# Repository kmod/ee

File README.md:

ee
==

A catchall repo for my more EE-related projects

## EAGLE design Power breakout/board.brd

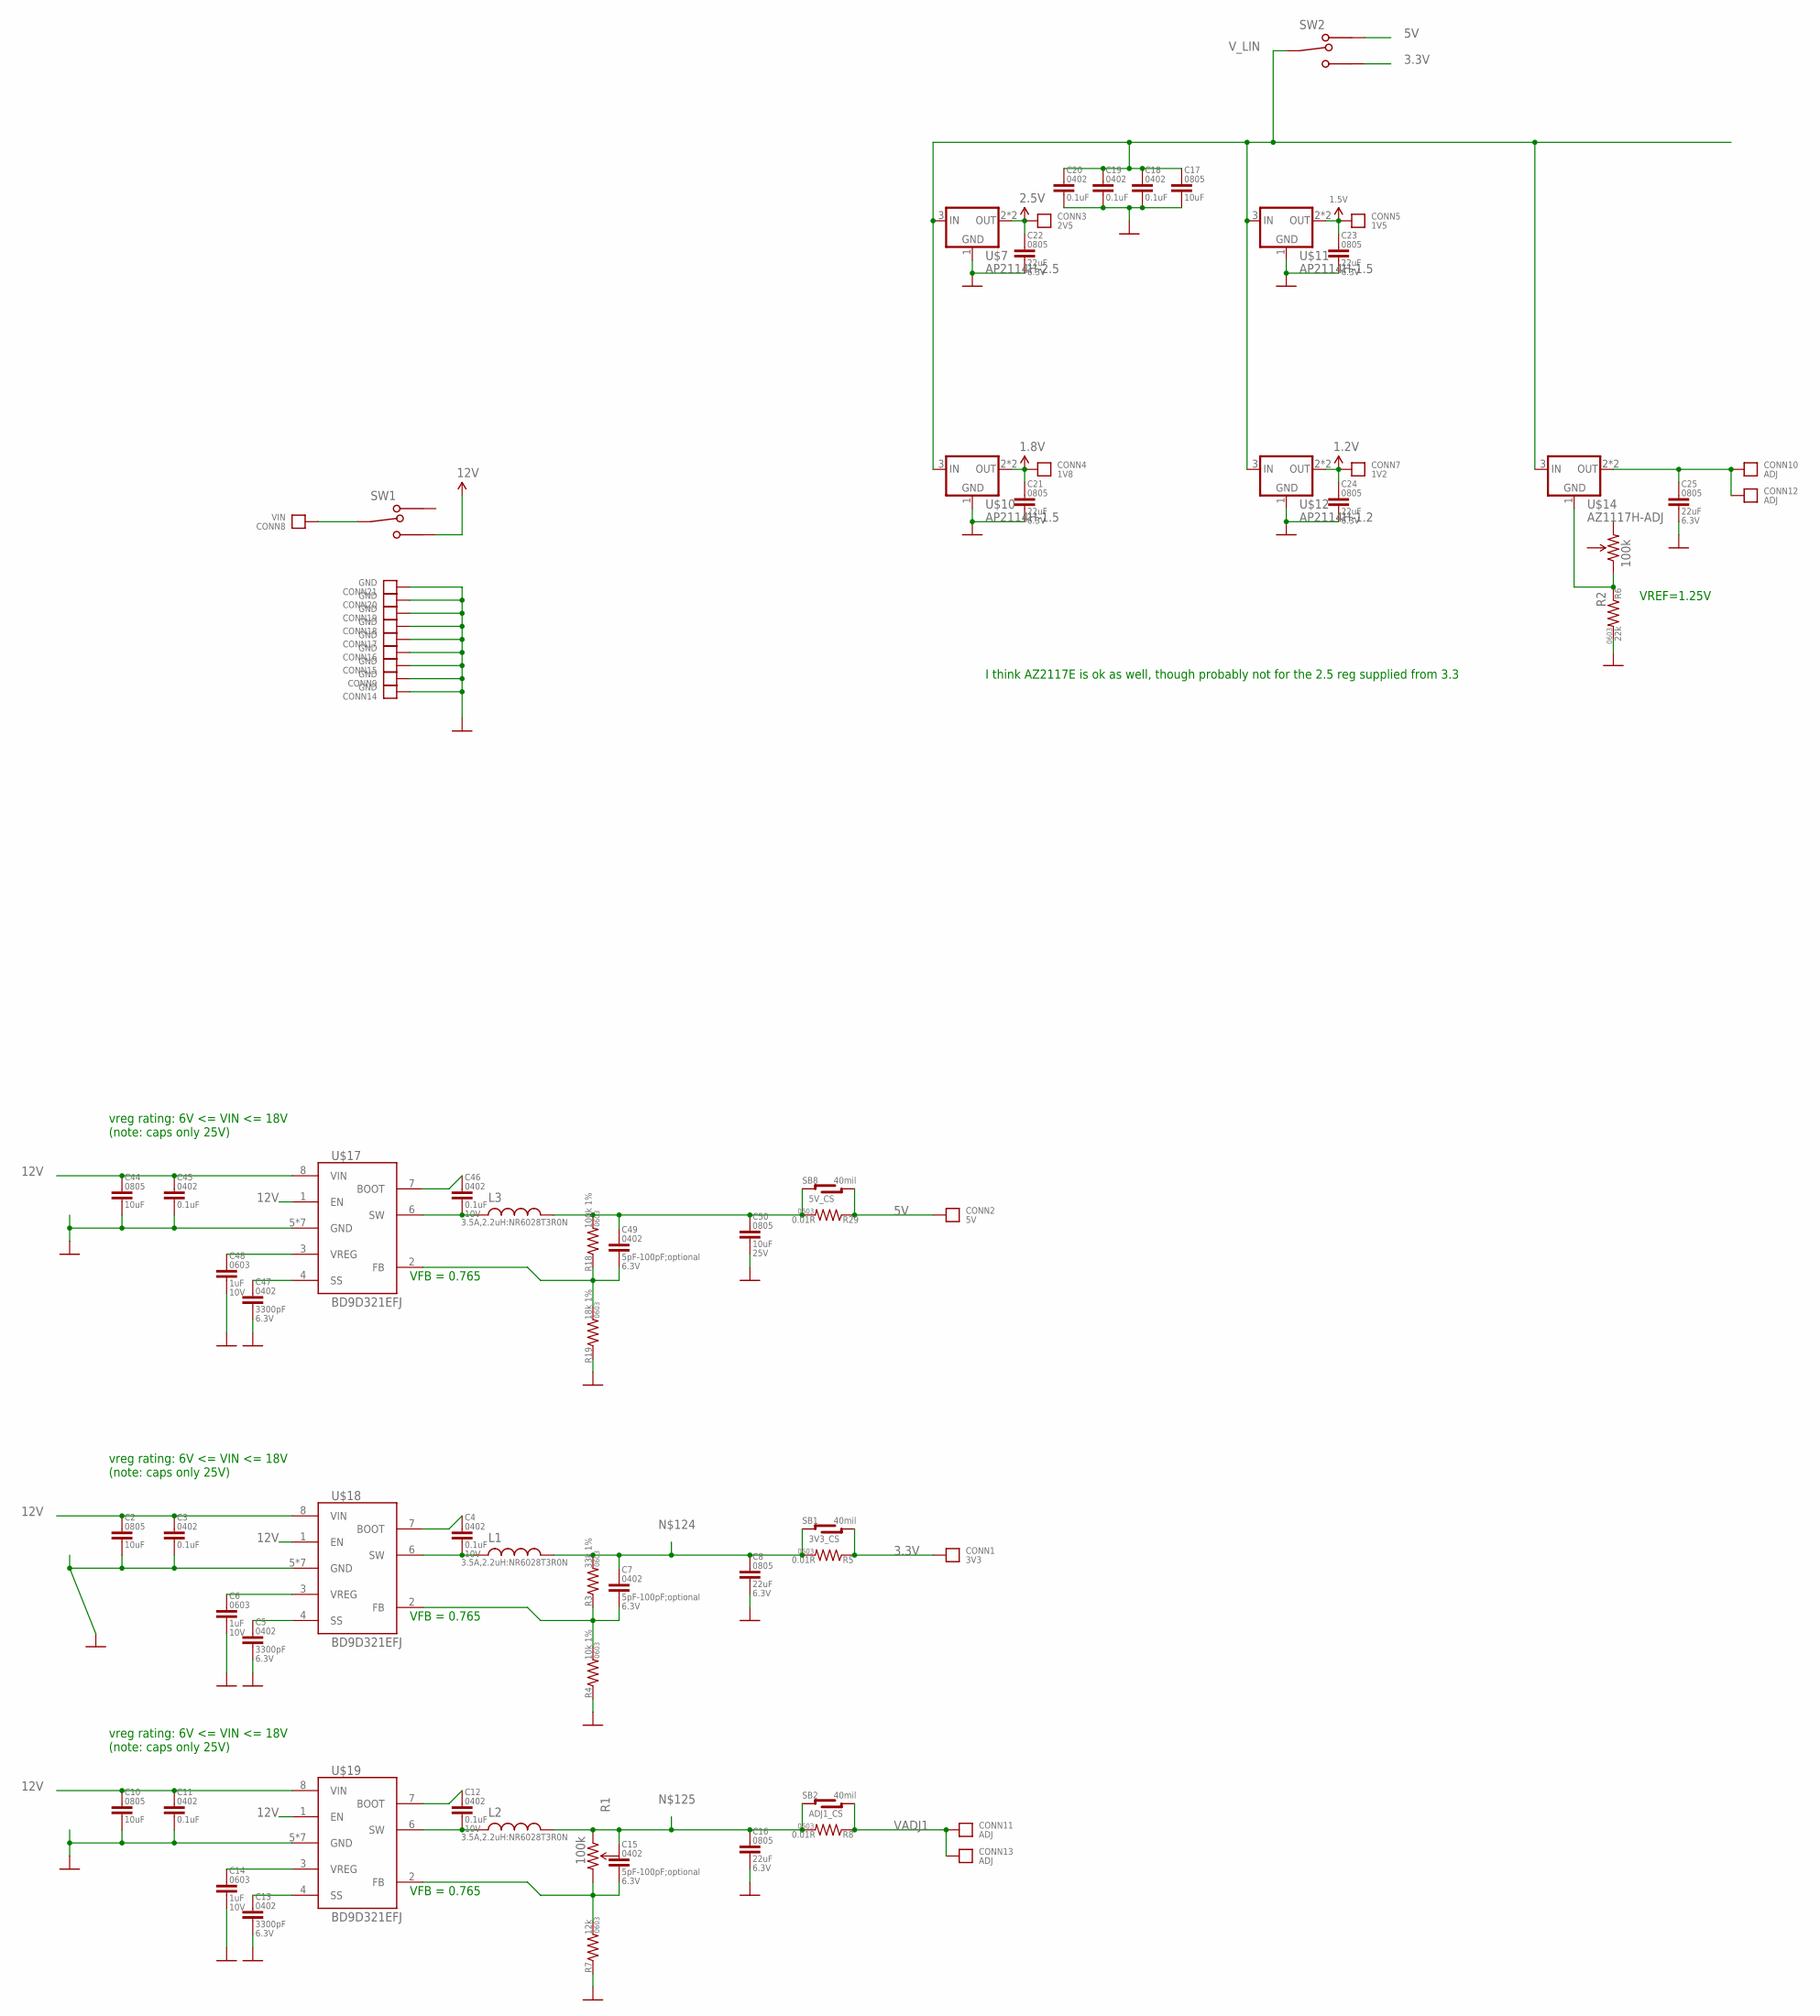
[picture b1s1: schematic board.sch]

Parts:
C2, C10, C17, C44, C50: 10uF; 0805-CAP; VOLTAGE 25V
C3, C11, C18, C19, C20, C45: 0.1uF; 0402-CAP; VOLTAGE 25V
C4, C12, C46: 0.1uF; 0402-CAP; VOLTAGE 10V
C5, C13, C47: 3300pF; 0402-CAP
C6, C14, C48: 1uF; 0603-CAP; VOLTAGE 10V
C7, C15, C49: 5pF-100pF;optional; 0402-CAP
C8, C16, C21, C22, C23, C24, C25: 22uF; 0805-CAP
CONN1: 3V3; HOLE_22AWG
CONN2: 5V; HOLE_22AWG
CONN3: 2V5; HOLE_22AWG
CONN4: 1V8; HOLE_22AWG
CONN5: 1V5; HOLE_22AWG
CONN7: 1V2; HOLE_22AWG
CONN8: VIN; HOLE_22AWG
CONN9, CONN14, CONN15, CONN16, CONN17, CONN18, CONN19, CONN20, CONN21: GND; HOLE_22AWG
CONN10, CONN11: ADJ; HOLE_22AWG
CONN12, CONN13: ADJ; HOLE_28AWG
L1, L2, L3: 3.5A,2.2uH:NR6028T3R0N; NR60XX
R1, R2: 100k; TRIM_POT_PTH
R3: 33k 1%; 0603-RES
R4: 10k 1%; 0603-RES
R5, R8, R29: 0.01R; 0603-RES
R6: 22k; 0603-RES
R7: 12k; 0603-RES
R18: 100k 1%; 0603-RES
R19: 18k 1%; 0603-RES
SB1: 3V3_CS; SOLDER-BRIDGE-OPEN-LARGE
SB2: ADJ1_CS; SOLDER-BRIDGE-OPEN-LARGE
SB8: 5V_CS; SOLDER-BRIDGE-OPEN-LARGE
SW1, SW2: SWITCH_SPDT; SWITCH_SLIDE_SPDT
U$7: AP2114H-2.5; SOT223
U$10, U$11: AP2114H-1.5; SOT223
U$12: AP2114H-1.2; SOT223
U$14: AZ1117H-ADJ; SOT223
U$17, U$18, U$19: BD9D321EFJ; HTSOP8

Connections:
1.2V: C24.1, CONN7.P, U$12.2 (OUT), U$12.4 (OUT)
1.5V: C23.1, CONN5.P, U$11.2 (OUT), U$11.4 (OUT)
1.8V: C21.1, CONN4.P, U$10.2 (OUT), U$10.4 (OUT)
2.5V: C22.1, CONN3.P, U$7.2 (OUT), U$7.4 (OUT)
3.3V: CONN1.P, R5.1, SB1.R1, SB1.R2, SW2.P2
3.3V_FB: C49.2, R18.1, R19.2, U$17.2 (FB)
3.3V_FB1: C7.2, R3.1, R4.2, U$18.2 (FB)
3.3V_FB2: C15.2, R1.3 (CW), R7.2, U$19.2 (FB)
5V: CONN2.P, R29.1, SB8.R1, SB8.R2, SW2.P1
12V: C2.1, C3.1, C10.1, C11.1, C44.1, C45.1, SW1.P2, U$17.1 (EN), U$17.8 (VIN), U$18.1 (EN), U$18.8 (VIN), U$19.1 (EN), U$19.8 (VIN)
GND: C2.2, C3.2, C5.2, C6.2, C8.2, C10.2, C11.2, C13.2, C14.2, C16.2, C17.2, C18.2, C19.2, C20.2, C21.2, C22.2, C23.2, C24.2, C25.2, C44.2, C45.2, C47.2, C48.2, C50.2, CONN9.P, CONN14.P, CONN15.P, CONN16.P, CONN17.P, CONN18.P, CONN19.P, CONN20.P, CONN21.P, R4.1, R6.2, R7.1, R19.1, U$7.1 (GND), U$10.1 (GND), U$11.1 (GND), U$12.1 (GND), U$17.5 (GND), U$17.P$1 (GND), U$17.P$2 (GND), U$17.P$3 (GND), U$17.P$4 (GND), U$17.P$5 (GND), U$17.PAD (GND), U$18.5 (GND), U$18.P$1 (GND), U$18.P$2 (GND), U$18.P$3 (GND), U$18.P$4 (GND), U$18.P$5 (GND), U$18.PAD (GND), U$19.5 (GND), U$19.P$1 (GND), U$19.P$2 (GND), U$19.P$3 (GND), U$19.P$4 (GND), U$19.P$5 (GND), U$19.PAD (GND)
unnamed: C25.1, CONN10.P, CONN12.P, U$14.2 (OUT), U$14.4 (OUT)
unnamed: C4.1, U$18.7 (BOOT)
unnamed: C4.2, L1.P$1 (1), U$18.6 (SW)
unnamed: C6.1, U$18.3 (VREG)
unnamed: C5.1, U$18.4 (SS)
unnamed: C12.1, U$19.7 (BOOT)
unnamed: C12.2, L2.P$1 (1), U$19.6 (SW)
unnamed: C14.1, U$19.3 (VREG)
unnamed: C13.1, U$19.4 (SS)
unnamed: R2.1 (CCW), R6.1, U$14.1 (GND)
unnamed: C46.2, L3.P$1 (1), U$17.6 (SW)
unnamed: C46.1, U$17.7 (BOOT)
unnamed: C48.1, U$17.3 (VREG)
unnamed: C47.1, U$17.4 (SS)
unnamed: C49.1, C50.1, L3.P$2 (2), R18.2, R29.2, SB8.L1, SB8.L2
unnamed: C7.1, C8.1, L1.P$2 (2), R3.2, R5.2, SB1.L1, SB1.L2
unnamed: C15.1, C16.1, L2.P$2 (2), R1.1 (CCW), R8.2, SB2.L1, SB2.L2
VADJ1: CONN11.P, CONN13.P, R8.1, SB2.R1, SB2.R2
VIN_UNSW: CONN8.P, SW1.C
V_LIN: C17.1, C18.1, C19.1, C20.1, SW2.C, U$7.3 (IN), U$10.3 (IN), U$11.3 (IN), U$12.3 (IN), U$14.3 (IN)

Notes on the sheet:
VFB = 0.765
vreg rating: 6V <= VIN <= 18V (note: caps only 25V)
VREF=1.25V
I think AZ2117E is ok as well, though probably not for the 2.5 reg supplied from 3.3

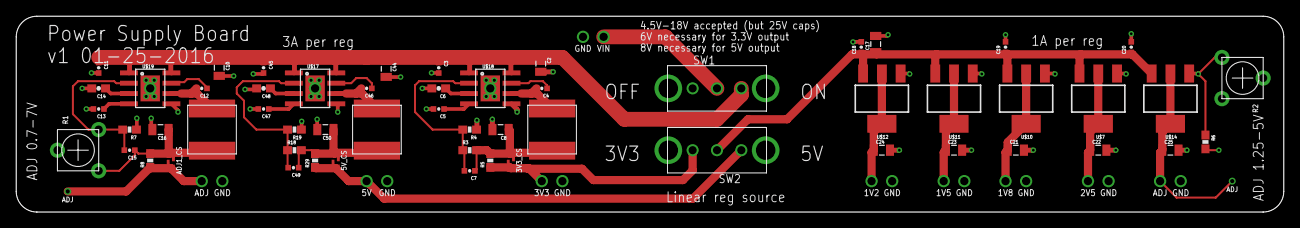
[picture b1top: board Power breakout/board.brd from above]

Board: 2 copper layers, 156.2 x 24.1 mm, 77 parts (0 on the bottom side), 31 nets.

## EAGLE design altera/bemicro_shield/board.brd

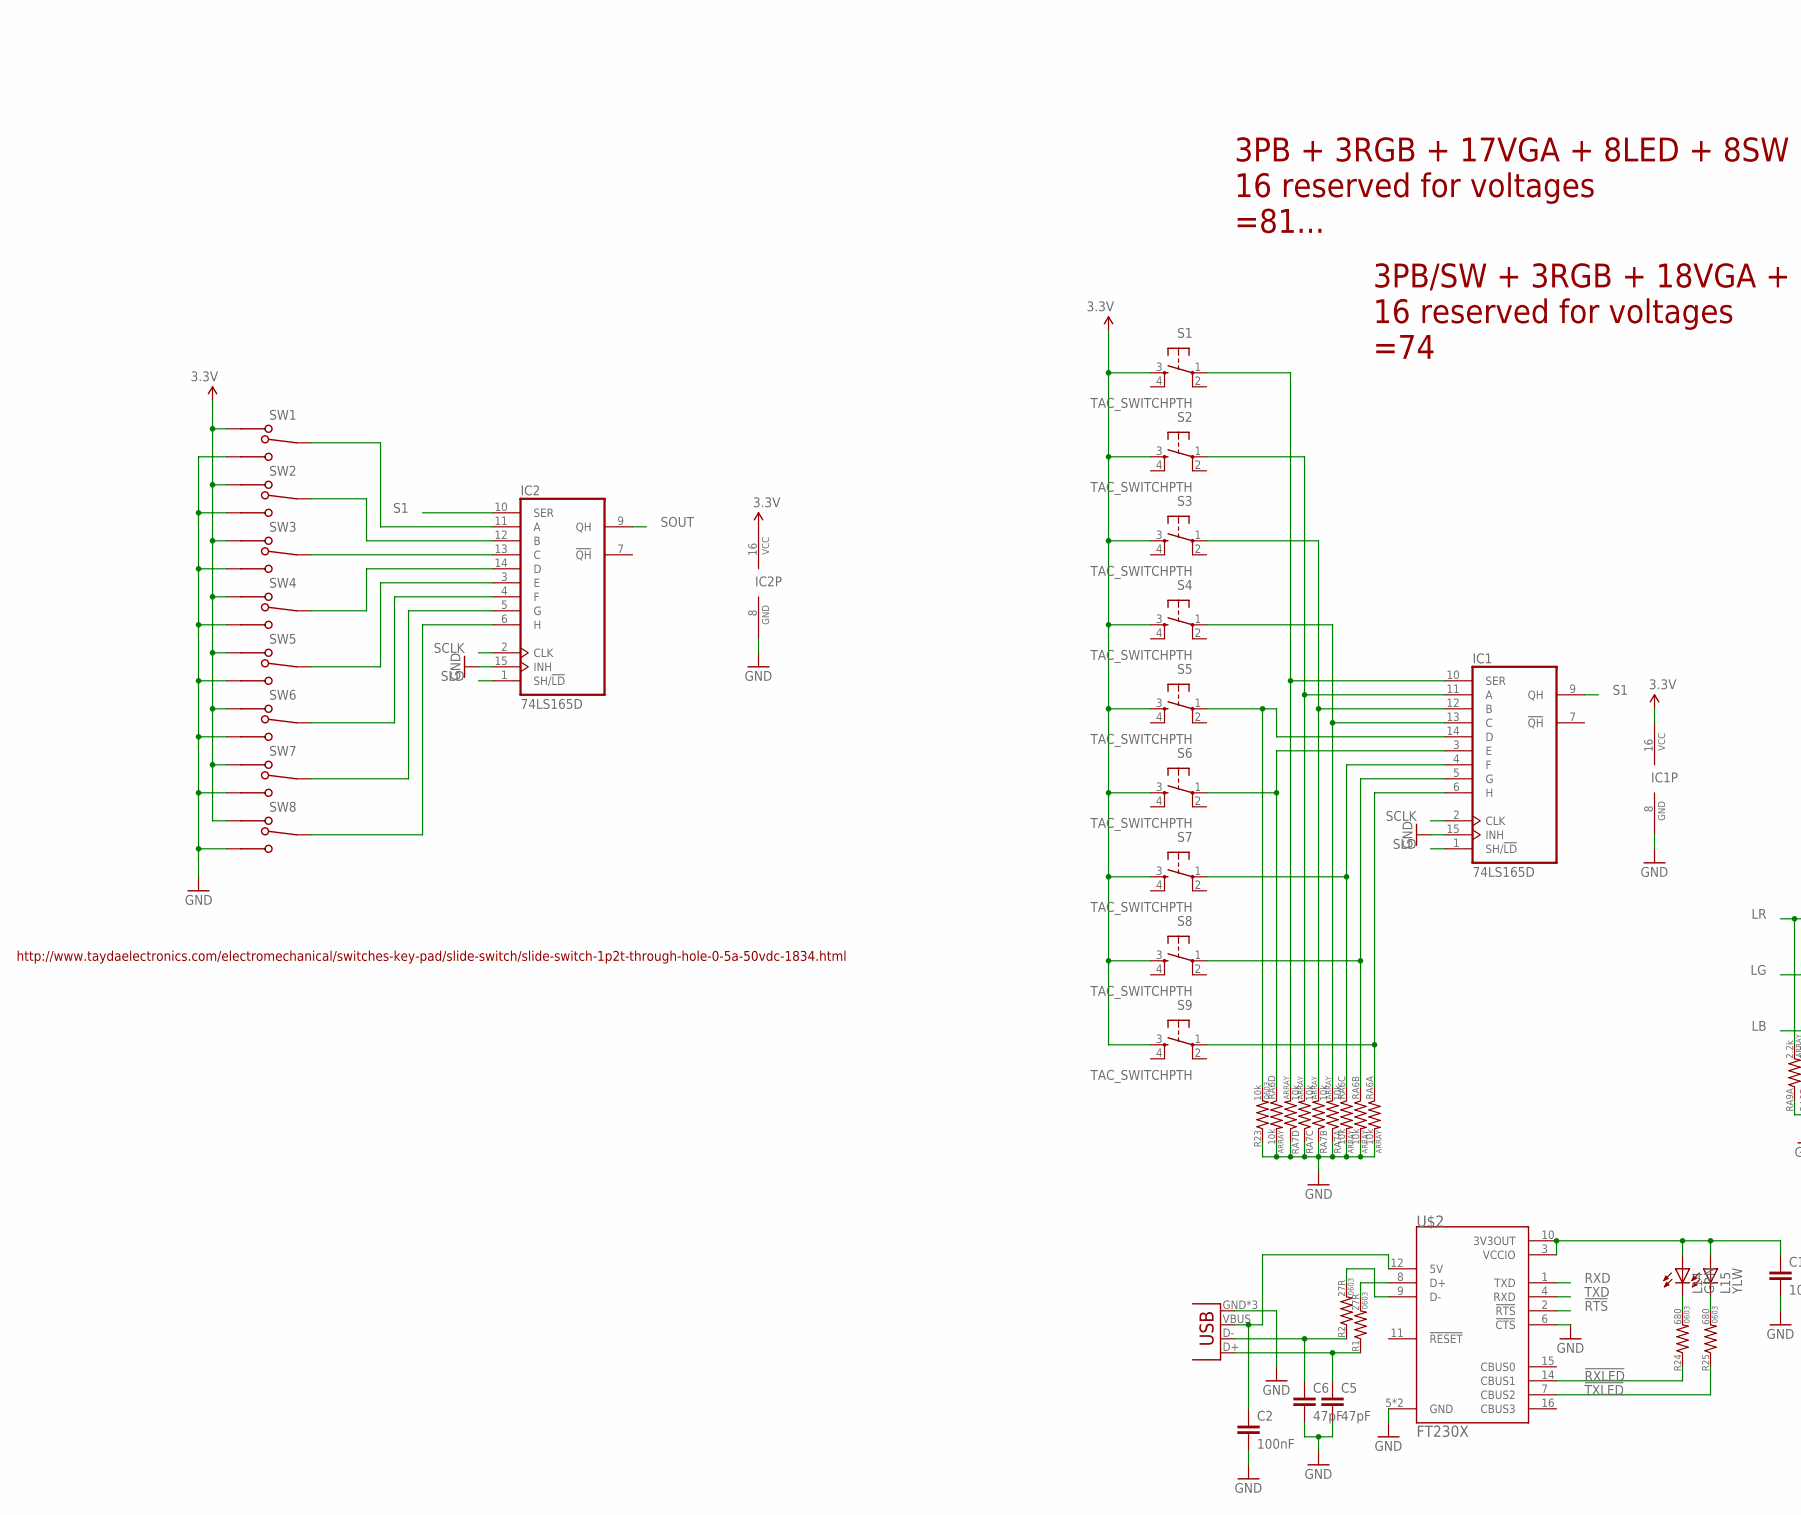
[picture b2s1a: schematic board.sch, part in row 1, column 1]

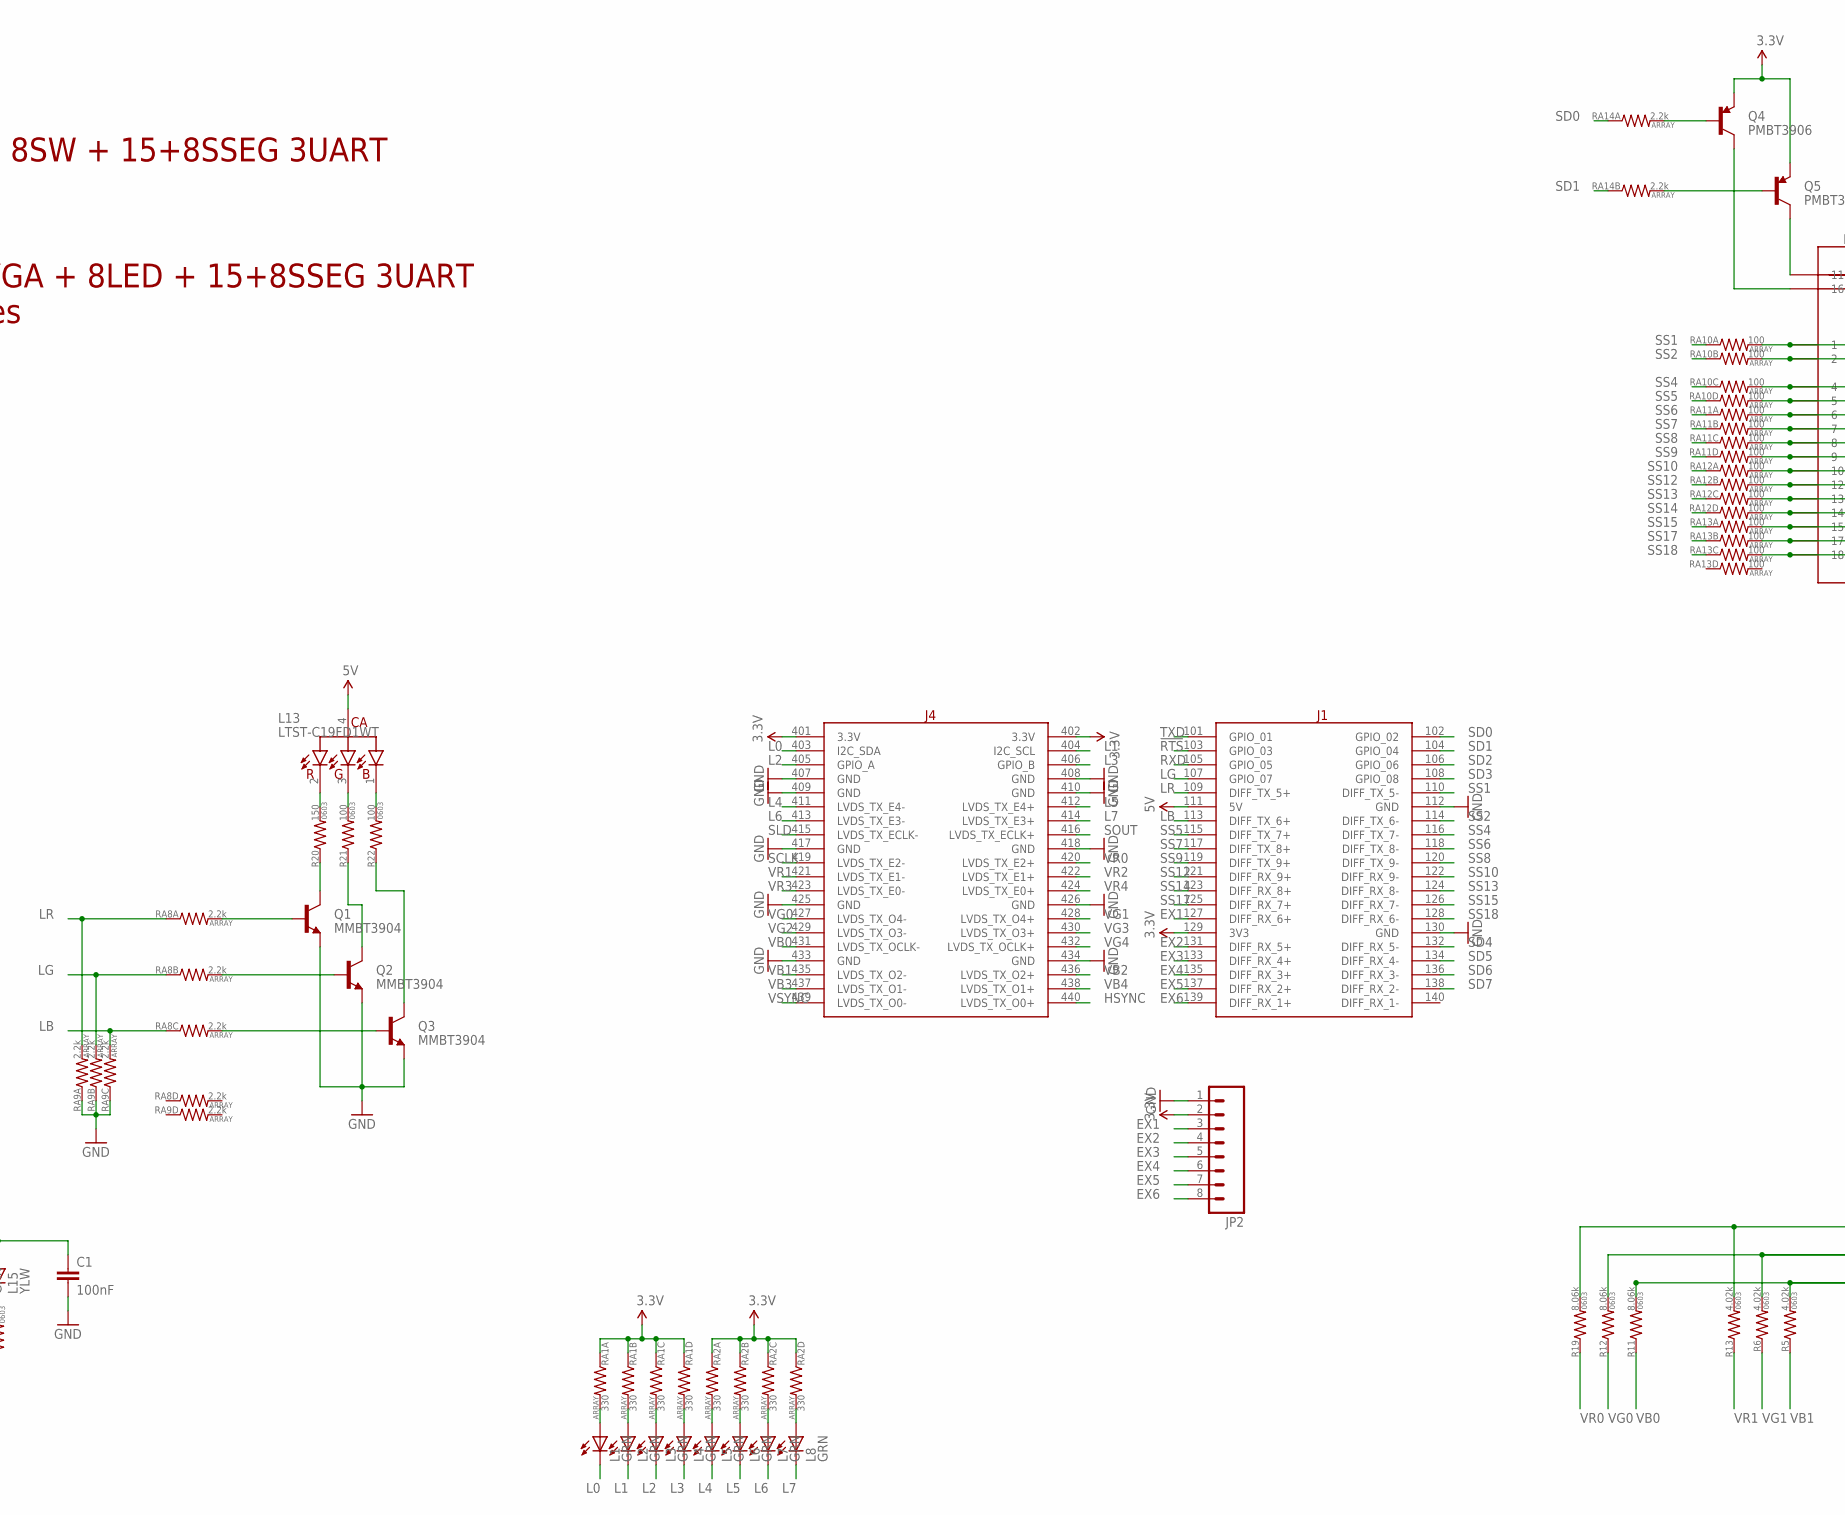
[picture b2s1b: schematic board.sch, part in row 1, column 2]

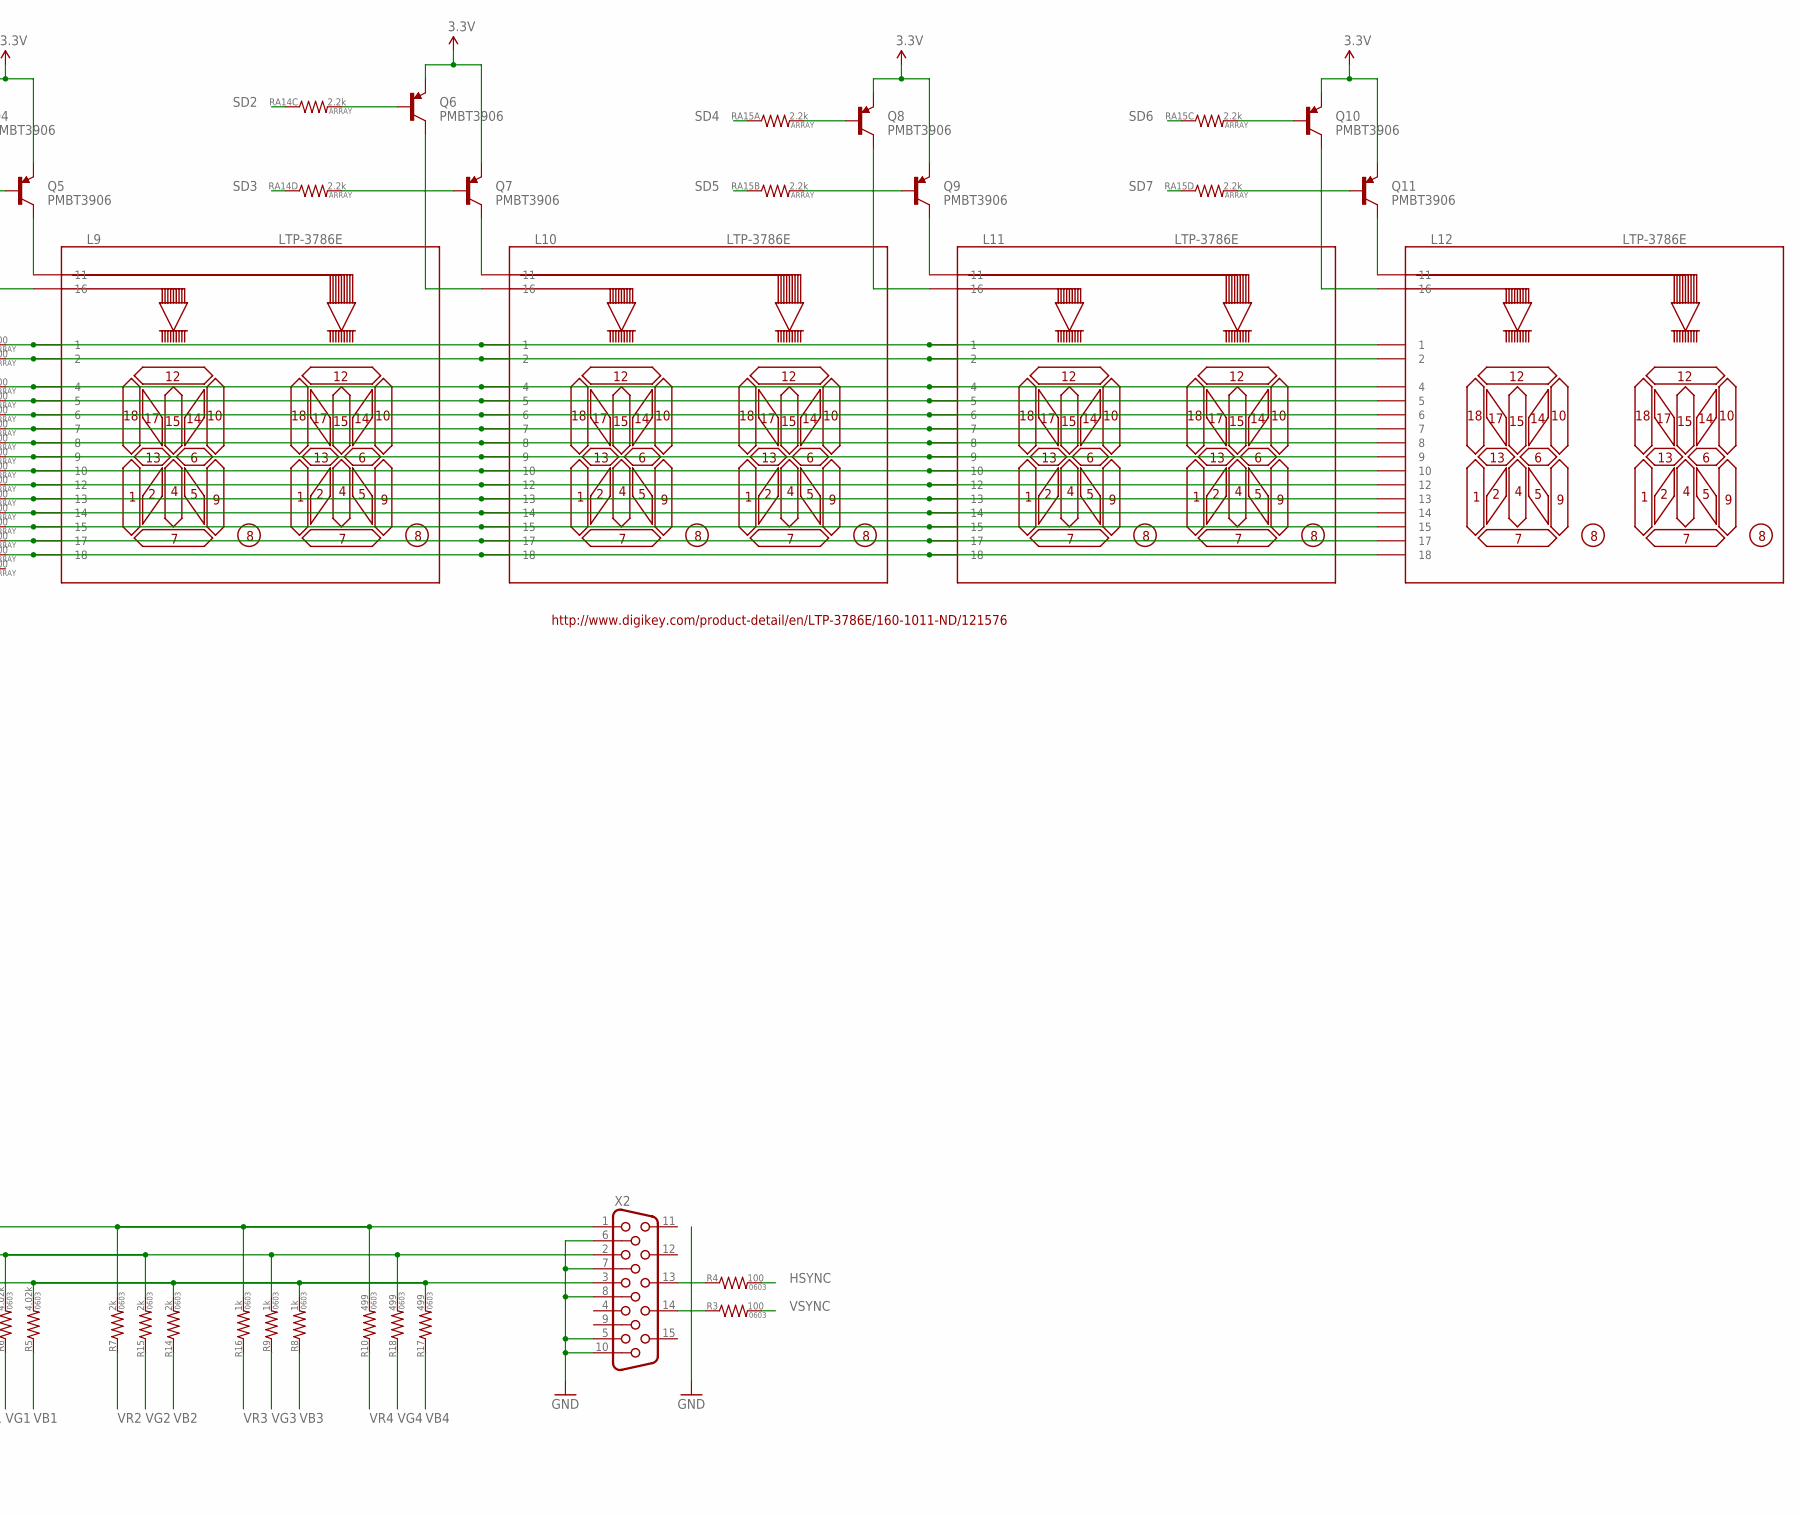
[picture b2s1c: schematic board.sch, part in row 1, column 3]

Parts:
C1, C2: 100nF; 0402-CAP
C5, C6: 47pF; 0402-CAP
IC1, IC2: 74LS165D; SO16
JP1: USB-MICROB
JP2: M081X08; 1X08
L1, L2, L3, L4, L5, L6, L7, L8, L14: GRN; 0603_LED
L9, L10, L11, L12: LTP-3786E; LTP-378?
L13: LTST-C19FD1WT; LTST-C19F
L15: YLW; 0603_LED
Q1, Q2, Q3: MMBT3904; SOT23
Q4, Q5, Q6, Q7, Q8, Q9, Q10, Q11: PMBT3906; SOT23-3
R1, R2: 27R; 0603-RES
R3, R4, R21, R22: 100; 0603-RES
R5, R6, R13: 4.02k; 0603-RES
R7, R14, R15: 2k; 0603-RES
R8, R9, R16: 1k; 0603-RES
R10, R17, R18: 499; 0603-RES
R11, R12, R19: 8.06k; 0603-RES
R20: 150; 0603-RES
R23: 10k; 0603-RES
R24, R25: 680; 0603-RES
RA1, RA2: 330; 0603-ARV
RA6, RA7: 10k; 0603-ARV
RA8, RA9, RA14, RA15: 2.2k; 0603-ARV
RA10, RA11, RA12, RA13: 100; 0603-ARV
S1, S2, S3, S4, S5, S6, S7, S8, S9: TAC_SWITCHPTH; TACTILE-PTH
SW1, SW2, SW3, SW4, SW5, SW6, SW7, SW8: SWITCH_SPDT; SWITCH_SLIDE_SPDT
U$2: FT230X; TSSOP16
U$3: BEMICROCV_SHIELD
X2: HDF15H

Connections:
3.3V: IC1.16 (VCC), IC2.16 (VCC), JP2.2, Q4.2 (E), Q5.2 (E), Q6.2 (E), Q7.2 (E), Q8.2 (E), Q9.2 (E), Q10.2 (E), Q11.2 (E), RA1.1, RA1.2 (1), RA1.3 (1), RA1.4 (1), RA2.1, RA2.2 (1), RA2.3 (1), RA2.4 (1), S1.3, S2.3, S3.3, S4.3, S5.3, S6.3, S7.3, S8.3, S9.3, SW1.P1, SW2.P1, SW3.P1, SW4.P1, SW5.P1, SW6.P1, SW7.P1, SW8.P1, U$3.129 (3V3), U$3.401 (3.3V), U$3.402 (3.3V)
5V: L13.4 (CA), U$3.111 (5V)
!RTS: U$2.2 (!RTS), U$3.103 (GPIO_03)
!RXLED: R24.1, U$2.14 (CBUS1)
!TXLED: R25.1, U$2.7 (CBUS2)
EX1: JP2.3, U$3.127 (DIFF_RX_6+)
EX2: JP2.4, U$3.131 (DIFF_RX_5+)
EX3: JP2.5, U$3.133 (DIFF_RX_4+)
EX4: JP2.6, U$3.135 (DIFF_RX_3+)
EX5: JP2.7, U$3.137 (DIFF_RX_2+)
EX6: JP2.8, U$3.139 (DIFF_RX_1+)
GND: C1.2, C2.2, C5.2, C6.2, IC1.8 (GND), IC1.15 (INH), IC2.8 (GND), IC2.15 (INH), JP1.GND, JP1.MT1 (GND), JP1.MT2 (GND), JP2.1, Q1.2 (E), Q2.2 (E), Q3.2 (E), R23.1, RA6.5 (2), RA6.6 (2), RA6.7 (2), RA6.8 (2), RA7.1, RA7.2 (1), RA7.3 (1), RA7.4 (1), RA9.1, RA9.2 (1), RA9.3 (1), SW1.P2, SW2.P2, SW3.P2, SW4.P2, SW5.P2, SW6.P2, SW7.P2, SW8.P2, U$2.5 (GND), U$2.6 (!CTS), U$2.13 (GND), U$3.112 (GND), U$3.130 (GND), U$3.407 (GND), U$3.408 (GND), U$3.409 (GND), U$3.410 (GND), U$3.417 (GND), U$3.418 (GND), U$3.425 (GND), U$3.426 (GND), U$3.433 (GND), U$3.434 (GND), X2.5, X2.6, X2.7, X2.8, X2.10
HSYNC: R4.2, U$3.440 (LVDS_TX_O0+)
L0: L1.C, U$3.403 (I2C_SDA)
L1: L2.C, U$3.404 (I2C_SCL)
L2: L3.C, U$3.405 (GPIO_A)
L3: L4.C, U$3.406 (GPIO_B)
L4: L5.C, U$3.411 (LVDS_TX_E4-)
L5: L6.C, U$3.412 (LVDS_TX_E4+)
L6: L7.C, U$3.413 (LVDS_TX_E3-)
L7: L8.C, U$3.414 (LVDS_TX_E3+)
LB: RA8.3 (1), RA9.6 (2), U$3.113 (DIFF_TX_6+)
LG: RA8.2 (1), RA9.7 (2), U$3.107 (GPIO_07)
LR: RA8.1, RA9.8 (2), U$3.109 (DIFF_TX_5+)
unnamed: L1.A, RA1.8 (2)
unnamed: L2.A, RA1.7 (2)
unnamed: L3.A, RA1.6 (2)
unnamed: L4.A, RA1.5 (2)
unnamed: L5.A, RA2.8 (2)
unnamed: L6.A, RA2.7 (2)
unnamed: L7.A, RA2.6 (2)
unnamed: L8.A, RA2.5 (2)
unnamed: IC2.11 (A), SW1.C
unnamed: IC2.12 (B), SW2.C
unnamed: IC2.13 (C), SW3.C
unnamed: IC2.14 (D), SW4.C
unnamed: IC2.3 (E), SW5.C
unnamed: IC2.4 (F), SW6.C
unnamed: IC2.5 (G), SW7.C
unnamed: IC2.6 (H), SW8.C
unnamed: Q2.3 (C), R21.1
unnamed: Q3.3 (C), R22.1
unnamed: C6.1, JP1.D-, R2.1
unnamed: C5.1, JP1.D+, R1.1
unnamed: R1.2, U$2.8 (D+)
unnamed: R2.2, U$2.9 (D-)
unnamed: L14.C, R24.2
unnamed: C2.1, JP1.VBUS, U$2.12 (5V)
unnamed: C1.1, L14.A, L15.A, U$2.3 (VCCIO), U$2.10 (3V3OUT)
unnamed: R3.1, X2.14
unnamed: R4.1, X2.13
unnamed: IC1.10 (SER), RA7.5 (2), S1.1
unnamed: IC1.14 (D), R23.2, S5.1
unnamed: IC1.3 (E), RA6.4 (1), S6.1
unnamed: IC1.4 (F), RA6.3 (1), S7.1
unnamed: IC1.5 (G), RA6.2 (1), S8.1
unnamed: L12.P$16 (16), Q10.3 (C)
unnamed: IC1.11 (A), RA7.6 (2), S2.1
unnamed: IC1.12 (B), RA7.7 (2), S3.1
unnamed: IC1.13 (C), RA7.8 (2), S4.1
unnamed: IC1.6 (H), RA6.1, S9.1
unnamed: L12.P$11 (11), Q11.3 (C)
unnamed: Q1.1 (B), RA8.8 (2)
unnamed: Q2.1 (B), RA8.7 (2)
unnamed: Q3.1 (B), RA8.6 (2)
unnamed: L13.2 (R), R20.2
unnamed: L13.3 (G), R21.2
unnamed: L13.1 (B), R22.2
unnamed: Q1.3 (C), R20.1
unnamed: L11.P$11 (11), Q9.3 (C)
unnamed: L11.P$16 (16), Q8.3 (C)
unnamed: L9.P$1 (1), L10.P$1 (1), L11.P$1 (1), L12.P$1 (1), RA10.8 (2)
unnamed: L9.P$2 (2), L10.P$2 (2), L11.P$2 (2), L12.P$2 (2), RA10.7 (2)
unnamed: L10.P$11 (11), Q7.3 (C)
unnamed: L9.P$4 (4), L10.P$4 (4), L11.P$4 (4), L12.P$4 (4), RA10.6 (2)
unnamed: L9.P$5 (5), L10.P$5 (5), L11.P$5 (5), L12.P$5 (5), RA10.5 (2)
unnamed: L9.P$6 (6), L10.P$6 (6), L11.P$6 (6), L12.P$6 (6), RA11.8 (2)
unnamed: L9.P$7 (7), L10.P$7 (7), L11.P$7 (7), L12.P$7 (7), RA11.7 (2)
unnamed: L9.P$8 (8), L10.P$8 (8), L11.P$8 (8), L12.P$8 (8), RA11.6 (2)
unnamed: L9.P$9 (9), L10.P$9 (9), L11.P$9 (9), L12.P$9 (9), RA11.5 (2)
unnamed: L9.P$10 (10), L10.P$10 (10), L11.P$10 (10), L12.P$10 (10), RA12.8 (2)
unnamed: L9.P$12 (12), L10.P$12 (12), L11.P$12 (12), L12.P$12 (12), RA12.7 (2)
unnamed: L9.P$13 (13), L10.P$13 (13), L11.P$13 (13), L12.P$13 (13), RA12.6 (2)
unnamed: L9.P$14 (14), L10.P$14 (14), L11.P$14 (14), L12.P$14 (14), RA12.5 (2)
unnamed: L9.P$15 (15), L10.P$15 (15), L11.P$15 (15), L12.P$15 (15), RA13.8 (2)
unnamed: L9.P$17 (17), L10.P$17 (17), L11.P$17 (17), L12.P$17 (17), RA13.7 (2)
unnamed: L9.P$18 (18), L10.P$18 (18), L11.P$18 (18), L12.P$18 (18), RA13.6 (2)
unnamed: L10.P$16 (16), Q6.3 (C)
unnamed: L15.C, R25.2
unnamed: L9.P$11 (11), Q5.3 (C)
unnamed: L9.P$16 (16), Q4.3 (C)
unnamed: Q10.1 (B), RA15.6 (2)
unnamed: Q11.1 (B), RA15.5 (2)
unnamed: Q8.1 (B), RA15.8 (2)
unnamed: Q9.1 (B), RA15.7 (2)
unnamed: Q6.1 (B), RA14.6 (2)
unnamed: Q7.1 (B), RA14.5 (2)
unnamed: Q4.1 (B), RA14.8 (2)
unnamed: Q5.1 (B), RA14.7 (2)
RXD: U$2.1 (TXD), U$3.105 (GPIO_05)
S1: IC1.9 (QH), IC2.10 (SER)
SCLK: IC1.2 (CLK), IC2.2 (CLK), U$3.419 (LVDS_TX_E2-)
SD0: RA14.1, U$3.102 (GPIO_02)
SD1: RA14.2 (1), U$3.104 (GPIO_04)
SD2: RA14.3 (1), U$3.106 (GPIO_06)
SD3: RA14.4 (1), U$3.108 (GPIO_08)
SD4: RA15.1, U$3.132 (DIFF_RX_5-)
SD5: RA15.2 (1), U$3.134 (DIFF_RX_4-)
SD6: RA15.3 (1), U$3.136 (DIFF_RX_3-)
SD7: RA15.4 (1), U$3.138 (DIFF_RX_2-)
SLD: IC1.1 (SH/!LD), IC2.1 (SH/!LD), U$3.415 (LVDS_TX_ECLK-)
SOUT: IC2.9 (QH), U$3.416 (LVDS_TX_ECLK+)
SS1: RA10.1, U$3.110 (DIFF_TX_5-)
SS2: RA10.2 (1), U$3.114 (DIFF_TX_6-)
SS4: RA10.3 (1), U$3.116 (DIFF_TX_7-)
SS5: RA10.4 (1), U$3.115 (DIFF_TX_7+)
SS6: RA11.1, U$3.118 (DIFF_TX_8-)
SS7: RA11.2 (1), U$3.117 (DIFF_TX_8+)
SS8: RA11.3 (1), U$3.120 (DIFF_TX_9-)
SS9: RA11.4 (1), U$3.119 (DIFF_TX_9+)
SS10: RA12.1, U$3.122 (DIFF_RX_9-)
SS12: RA12.2 (1), U$3.121 (DIFF_RX_9+)
SS13: RA12.3 (1), U$3.124 (DIFF_RX_8-)
SS14: RA12.4 (1), U$3.123 (DIFF_RX_8+)
SS15: RA13.1, U$3.126 (DIFF_RX_7-)
SS17: RA13.2 (1), U$3.125 (DIFF_RX_7+)
SS18: RA13.3 (1), U$3.128 (DIFF_RX_6-)
TXD: U$2.4 (RXD), U$3.101 (GPIO_01)
VB0: R11.1, U$3.431 (LVDS_TX_OCLK-)
VB1: R5.1, U$3.435 (LVDS_TX_O2-)
VB2: R14.1, U$3.436 (LVDS_TX_O2+)
VB3: R8.1, U$3.437 (LVDS_TX_O1-)
VB4: R17.1, U$3.438 (LVDS_TX_O1+)
VBOUT: R5.2, R8.2, R11.2, R14.2, R17.2, X2.3
VG0: R12.1, U$3.427 (LVDS_TX_O4-)
VG1: R6.1, U$3.428 (LVDS_TX_O4+)
VG2: R15.1, U$3.429 (LVDS_TX_O3-)
VG3: R9.1, U$3.430 (LVDS_TX_O3+)
VG4: R18.1, U$3.432 (LVDS_TX_OCLK+)
VGOUT: R6.2, R9.2, R12.2, R15.2, R18.2, X2.2
VR0: R19.1, U$3.420 (LVDS_TX_E2+)
VR1: R13.1, U$3.421 (LVDS_TX_E1-)
VR2: R7.1, U$3.422 (LVDS_TX_E1+)
VR3: R16.1, U$3.423 (LVDS_TX_E0-)
VR4: R10.1, U$3.424 (LVDS_TX_E0+)
VROUT: R7.2, R10.2, R13.2, R16.2, R19.2, X2.1
VSYNC: R3.2, U$3.439 (LVDS_TX_O0-)

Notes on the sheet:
http://www.taydaelectronics.com/electromechanical/switches-key-pad/slide-switch/slide-switch-1p2t-through-hole-0-5a-50vdc-1834.html
http://www.digikey.com/product-detail/en/LTP-3786E/160-1011-ND/121576
3PB + 3RGB + 17VGA + 8LED + 8SW + 15+8SSEG 3UART 16 reserved for voltages =81...
3PB/SW + 3RGB + 18VGA + 8LED + 15+8SSEG 3UART 16 reserved for voltages =74

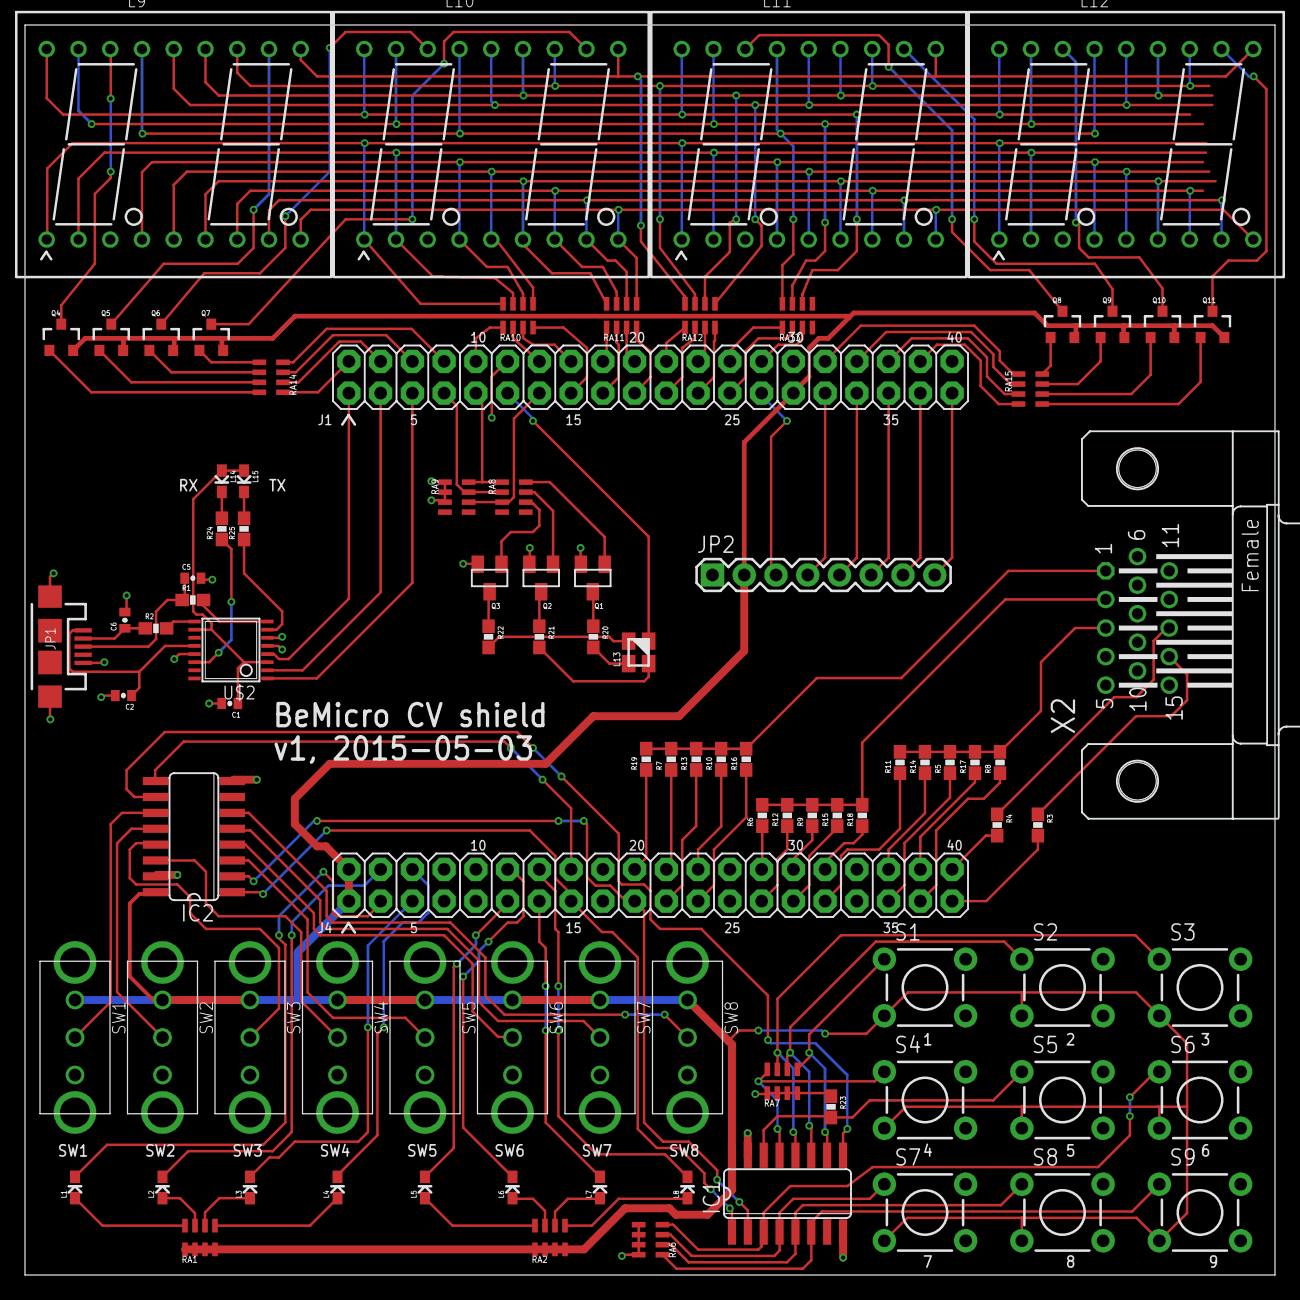
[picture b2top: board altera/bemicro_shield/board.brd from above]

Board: 2 copper layers, 100.0 x 100.0 mm, 91 parts (0 on the bottom side), 147 nets.

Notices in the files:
parts and their libraries:
SparkFun-Electromechanical: Licensing: Creative Commons ShareAlike 4.0 International - https://creativecommons.org/licenses/by-sa/4.0
SparkFun-Connectors: Licensing: CC v3.0 Share-Alike You are welcome to use this library for commercial purposes.
